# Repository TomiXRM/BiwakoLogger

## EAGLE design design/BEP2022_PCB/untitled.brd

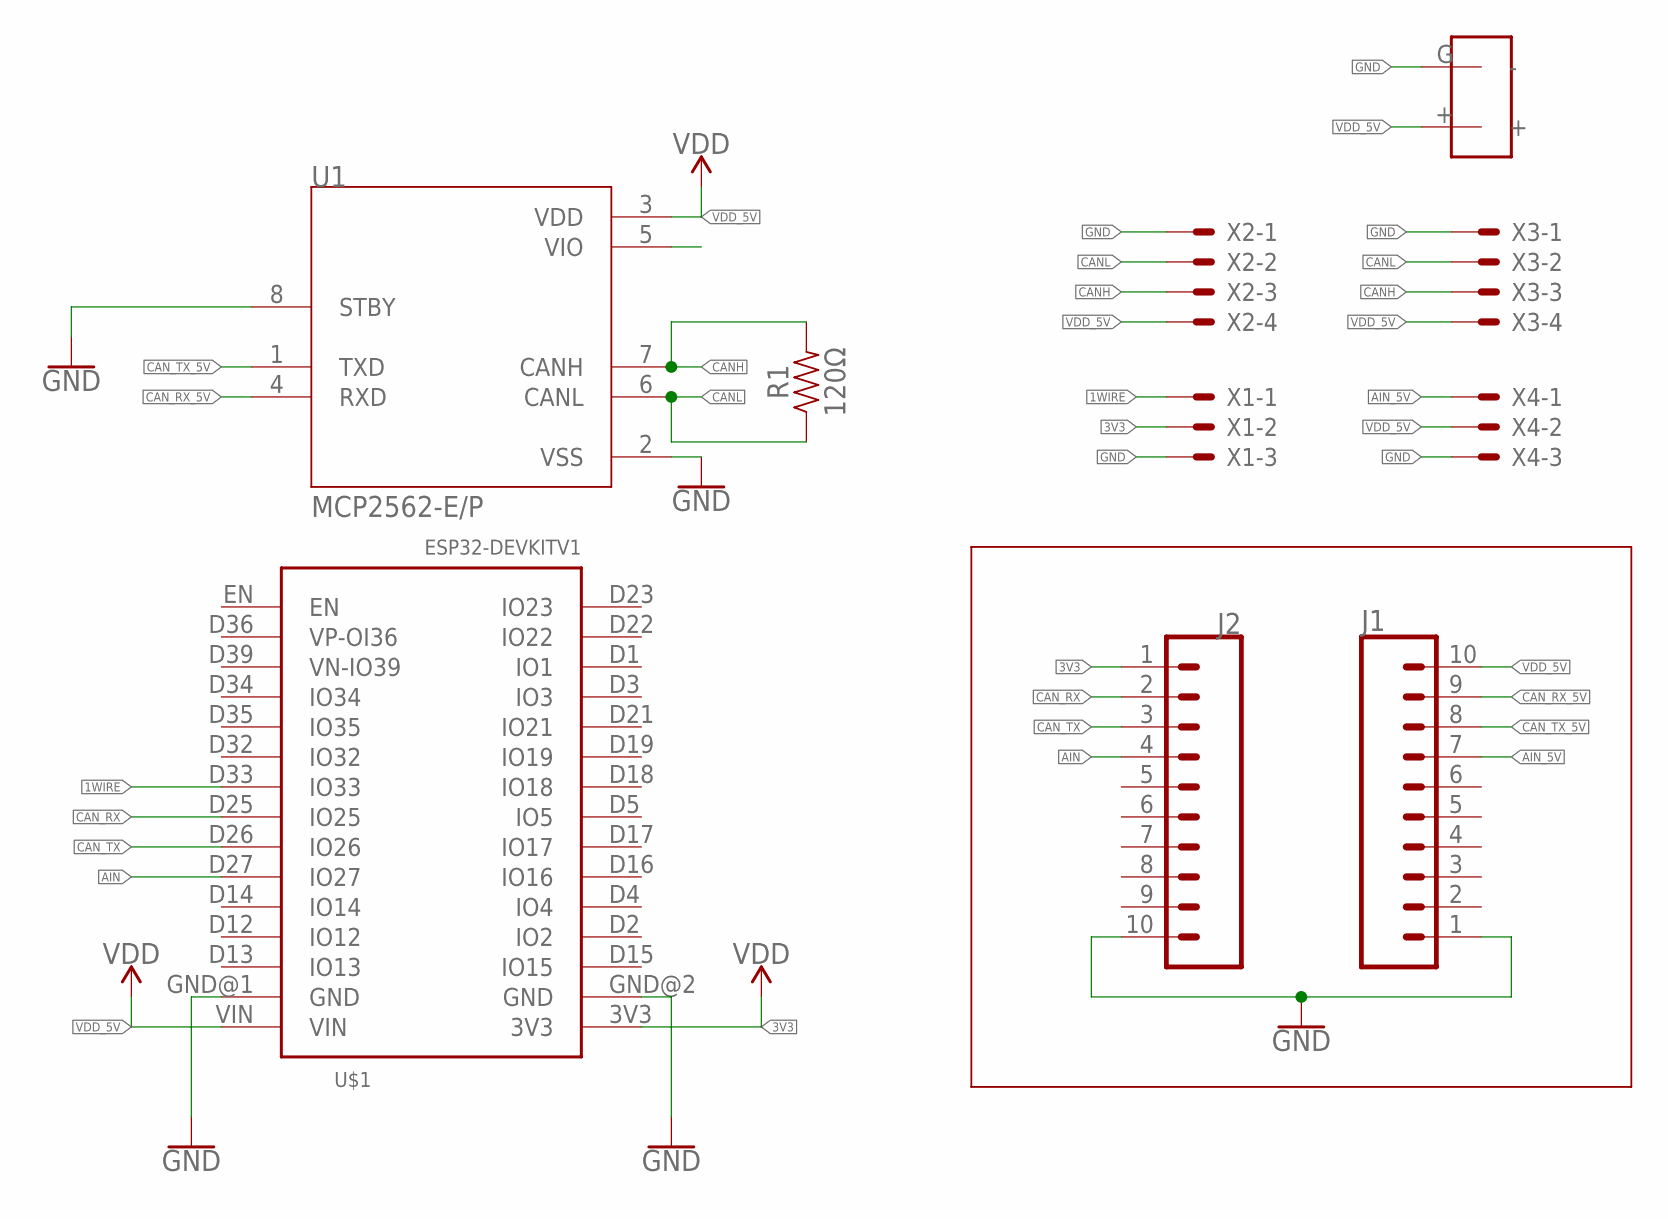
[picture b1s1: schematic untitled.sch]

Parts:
J1, J2: CONN_10"; 1X10
R1: 120Ω; AXIAL-0.3
U1: MCP2562-E/P; DIP787W45P254L1016H533Q8
U$1: ESP32DEVKITV1; ESP32-DEVKITV1
U$2: BAT
X1, X4: JST-XH-03-PIN-LONG-PAD; JST-XH-03-PACKAGE-LONG-PAD
X2, X3: JST-XH-04-PIN-LONG-PAD; JST-XH-04-PACKAGE-LONG-PAD

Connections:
1WIRE: U$1.D33 (IO33), X1.1
3V3: J2.1, U$1.3V3, X1.2
AIN: J2.4, U$1.D27 (IO27)
AIN_5V: J1.7, X4.1
CANH: R1.P$2 (2), U1.7 (CANH), X2.3, X3.3
CANL: R1.P$1 (1), U1.6 (CANL), X2.2, X3.2
CAN_RX: J2.2, U$1.D25 (IO25)
CAN_RX_5V: J1.9, U1.4 (RXD)
CAN_TX: J2.3, U$1.D26 (IO26)
CAN_TX_5V: J1.8, U1.1 (TXD)
GND: J1.1, J2.10, U1.2 (VSS), U1.8 (STBY), U$1.GND@1 (GND), U$1.GND@2 (GND), U$2.G (-), X1.3, X2.1, X3.1, X4.3
VDD_5V: J1.10, U1.3 (VDD), U$1.VIN, U$2.+, X2.4, X3.4, X4.2

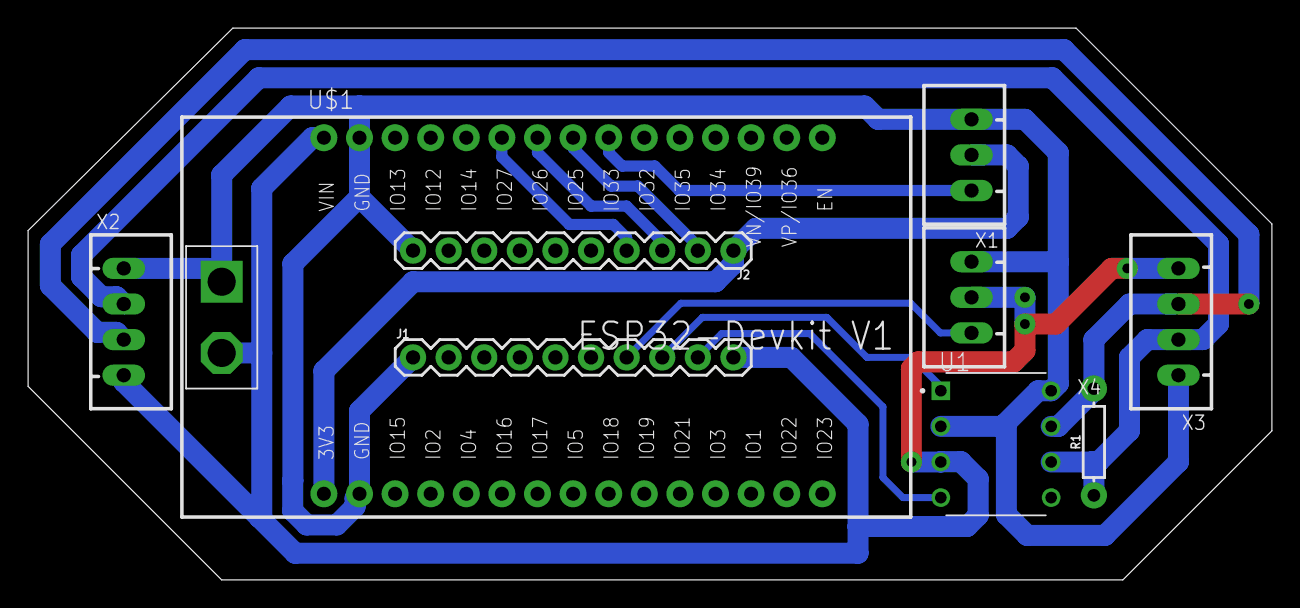
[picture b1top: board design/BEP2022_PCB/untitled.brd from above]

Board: 2 copper layers, 88.7 x 39.4 mm, 10 parts (0 on the bottom side), 12 nets.

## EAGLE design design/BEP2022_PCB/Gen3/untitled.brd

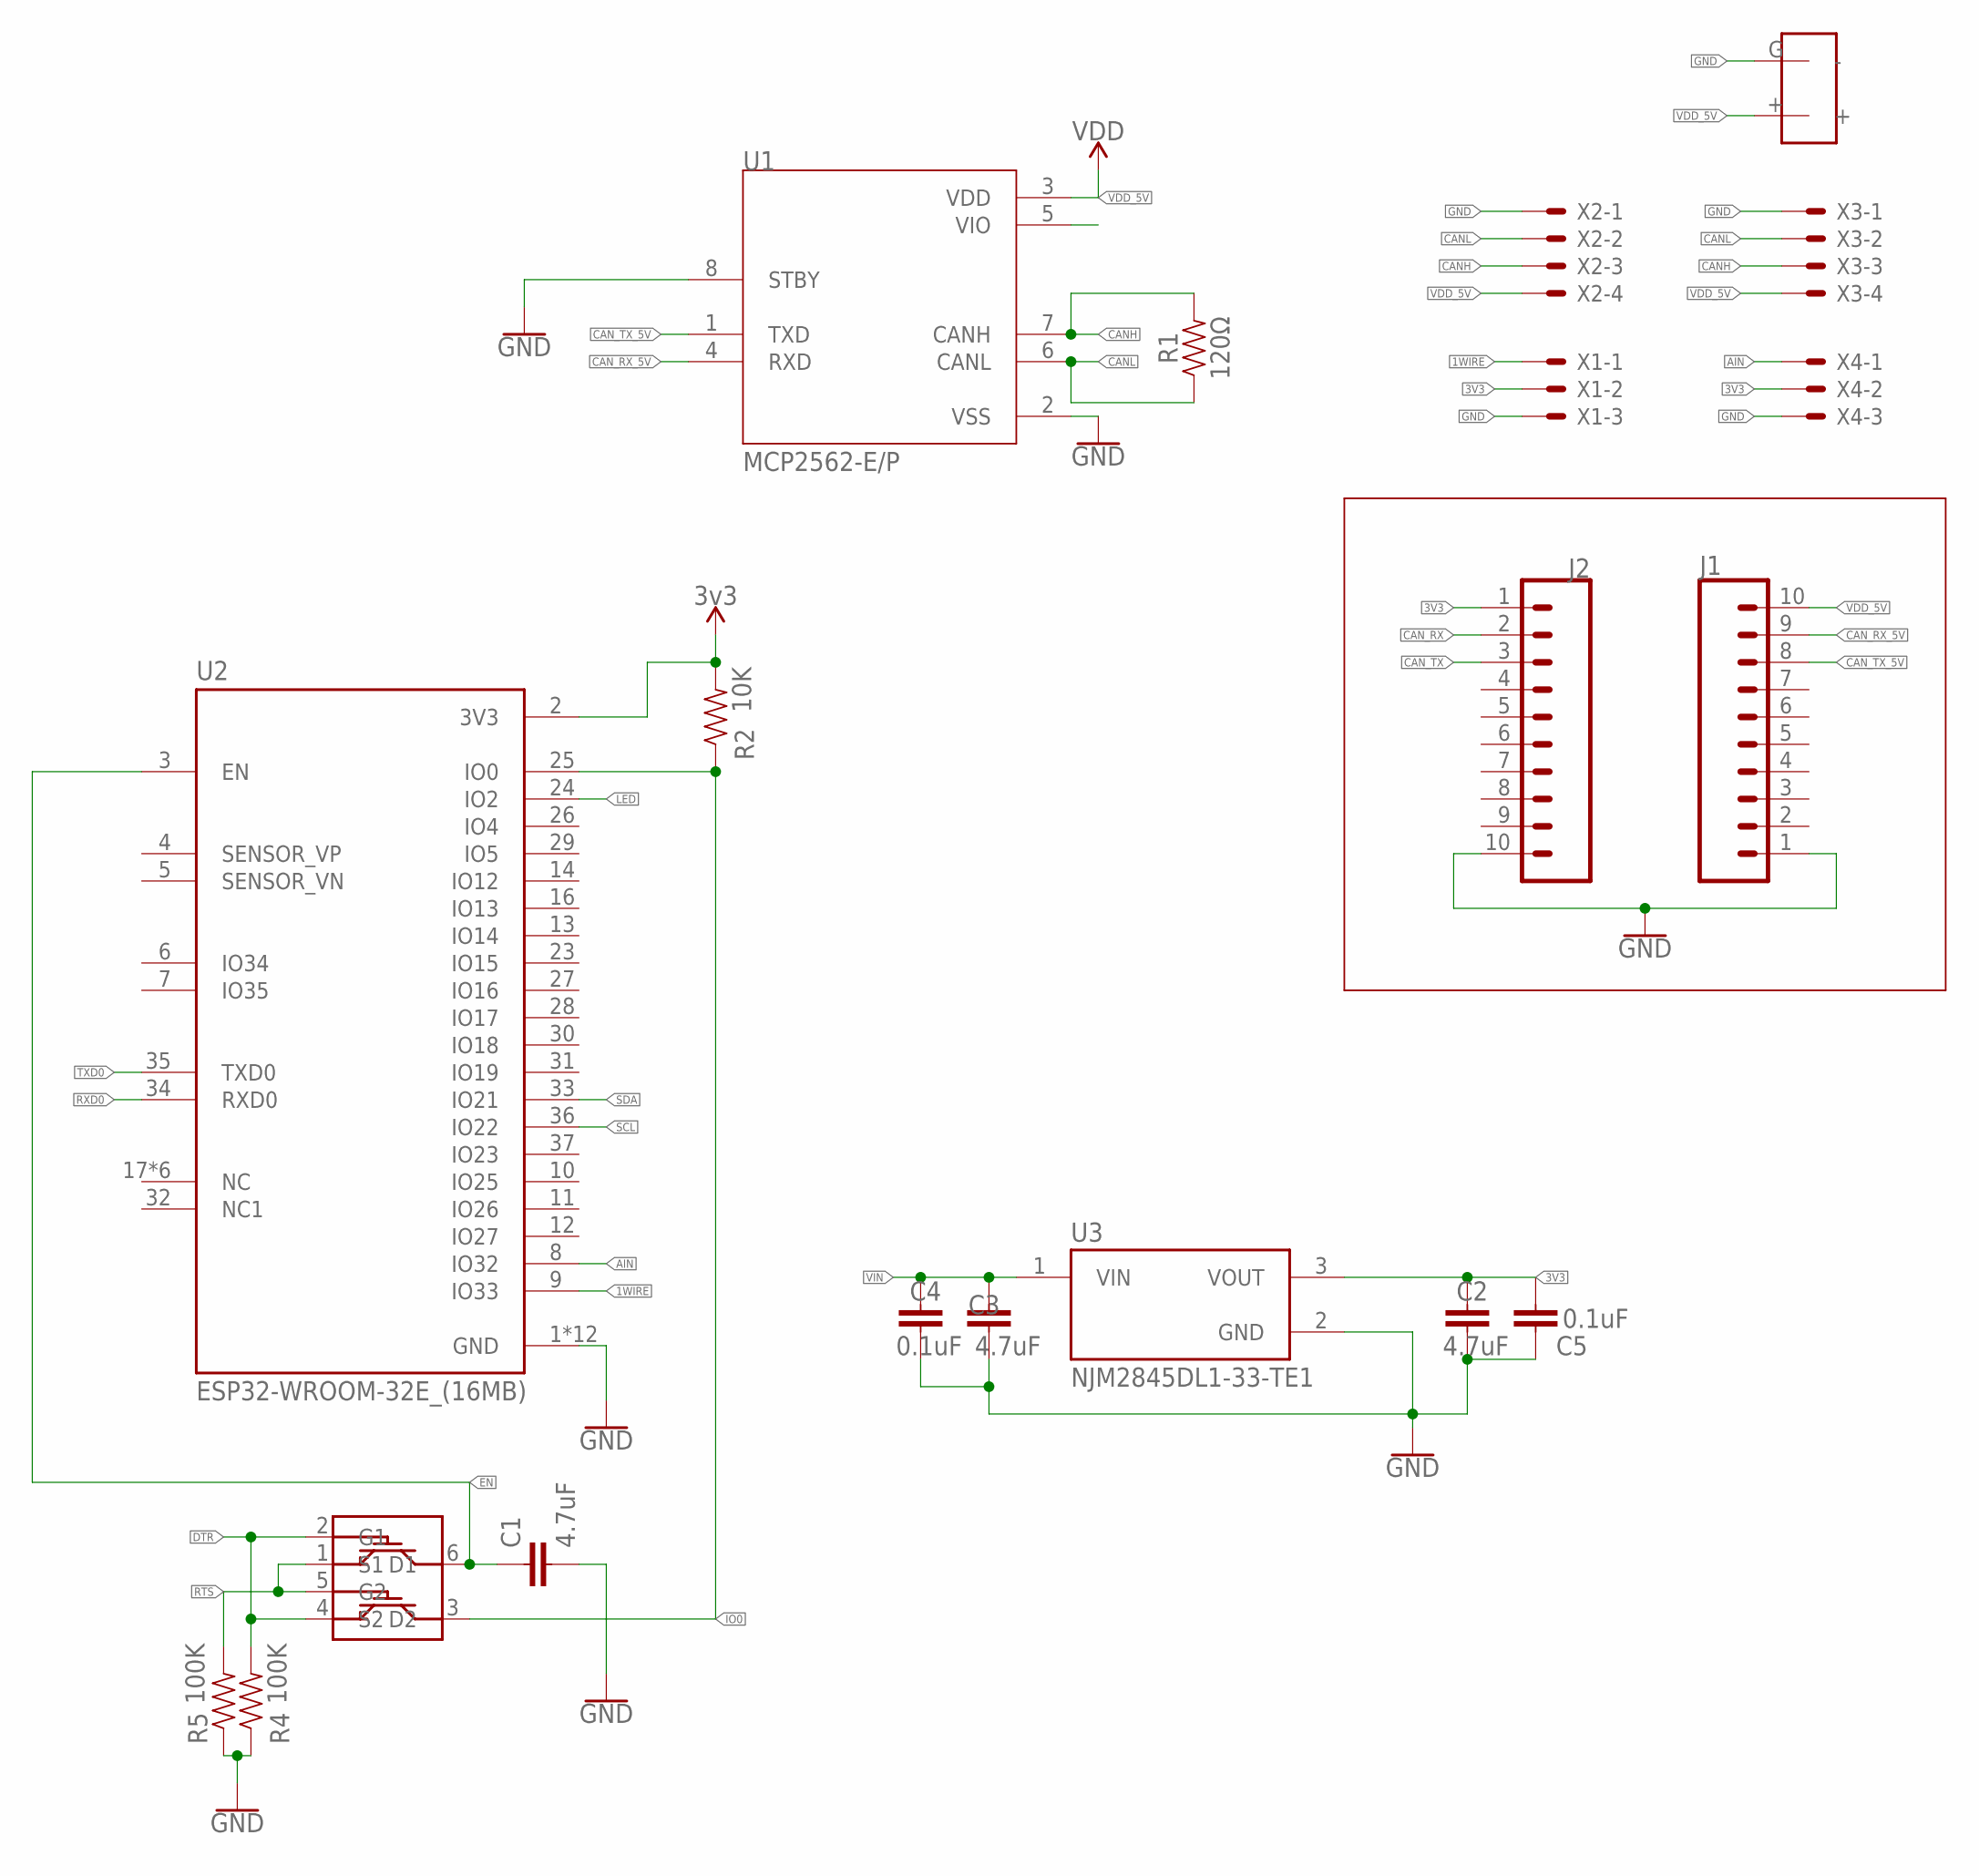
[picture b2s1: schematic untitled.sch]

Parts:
C1, C2, C3: 4.7uF; 0603
C4, C5: 0.1uF; 0603
J1, J2: CONN_10"; 1X10
R1: 120Ω; AXIAL-0.3
R2: 10K; 0603
R4, R5: 100K; 0603
U1: MCP2562-E/P; DIP787W45P254L1016H533Q8
U2: ESP32-WROOM-32E_(16MB); XCVR_ESP32-WROOM-32E_(16MB)
U3: NJM2845DL1-33-TE1; DPAK228P968X238-4N
U$1: 2N7002DW; SOT363
U$2: BAT
X1, X4: JST-XH-03-PIN-LONG-PAD; JST-XH-03-PACKAGE-LONG-PAD
X2, X3: JST-XH-04-PIN-LONG-PAD; JST-XH-04-PACKAGE-LONG-PAD

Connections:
1WIRE: U2.9 (IO33), X1.1
3V3: C2.1, C5.2, J2.1, R2.2, U2.2 (3V3), U3.3 (VOUT), X1.2, X4.2
AIN: U2.8 (IO32), X4.1
CANH: R1.P$2 (2), U1.7 (CANH), X2.3, X3.3
CANL: R1.P$1 (1), U1.6 (CANL), X2.2, X3.2
CAN_RX: J2.2
CAN_RX_5V: J1.9, U1.4 (RXD)
CAN_TX: J2.3
CAN_TX_5V: J1.8, U1.1 (TXD)
DTR: R4.2, U$1.2 (G1), U$1.4 (S2)
EN: C1.1, U2.3 (EN), U$1.6 (D1)
GND: C1.2, C2.2, C3.1, C4.2, C5.1, J1.1, J2.10, U1.2 (VSS), U1.8 (STBY), U2.1 (GND), U2.15 (GND), U2.38 (GND), U2.39_1 (GND), U2.39_2 (GND), U2.39_3 (GND), U2.39_4 (GND), U2.39_5 (GND), U2.39_6 (GND), U2.39_7 (GND), U2.39_8 (GND), U2.39_9 (GND), U3.2 (GND), U$2.G (-), X1.3, X2.1, X3.1, X4.3
IO0: R2.1, U2.25 (IO0), U$1.3 (D2)
LED: U2.24 (IO2)
unnamed: R4.1, R5.1
RTS: R5.2, U$1.1 (S1), U$1.5 (G2)
RXD0: U2.34 (RXD0)
SCL: U2.36 (IO22)
SDA: U2.33 (IO21)
TXD0: U2.35 (TXD0)
VDD_5V: J1.10, U1.3 (VDD), U$2.+, X2.4, X3.4
VIN: C3.2, C4.1, U3.1 (VIN)

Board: 2 copper layers, 20 parts (2 on the bottom side), 15 nets, no tracks yet.

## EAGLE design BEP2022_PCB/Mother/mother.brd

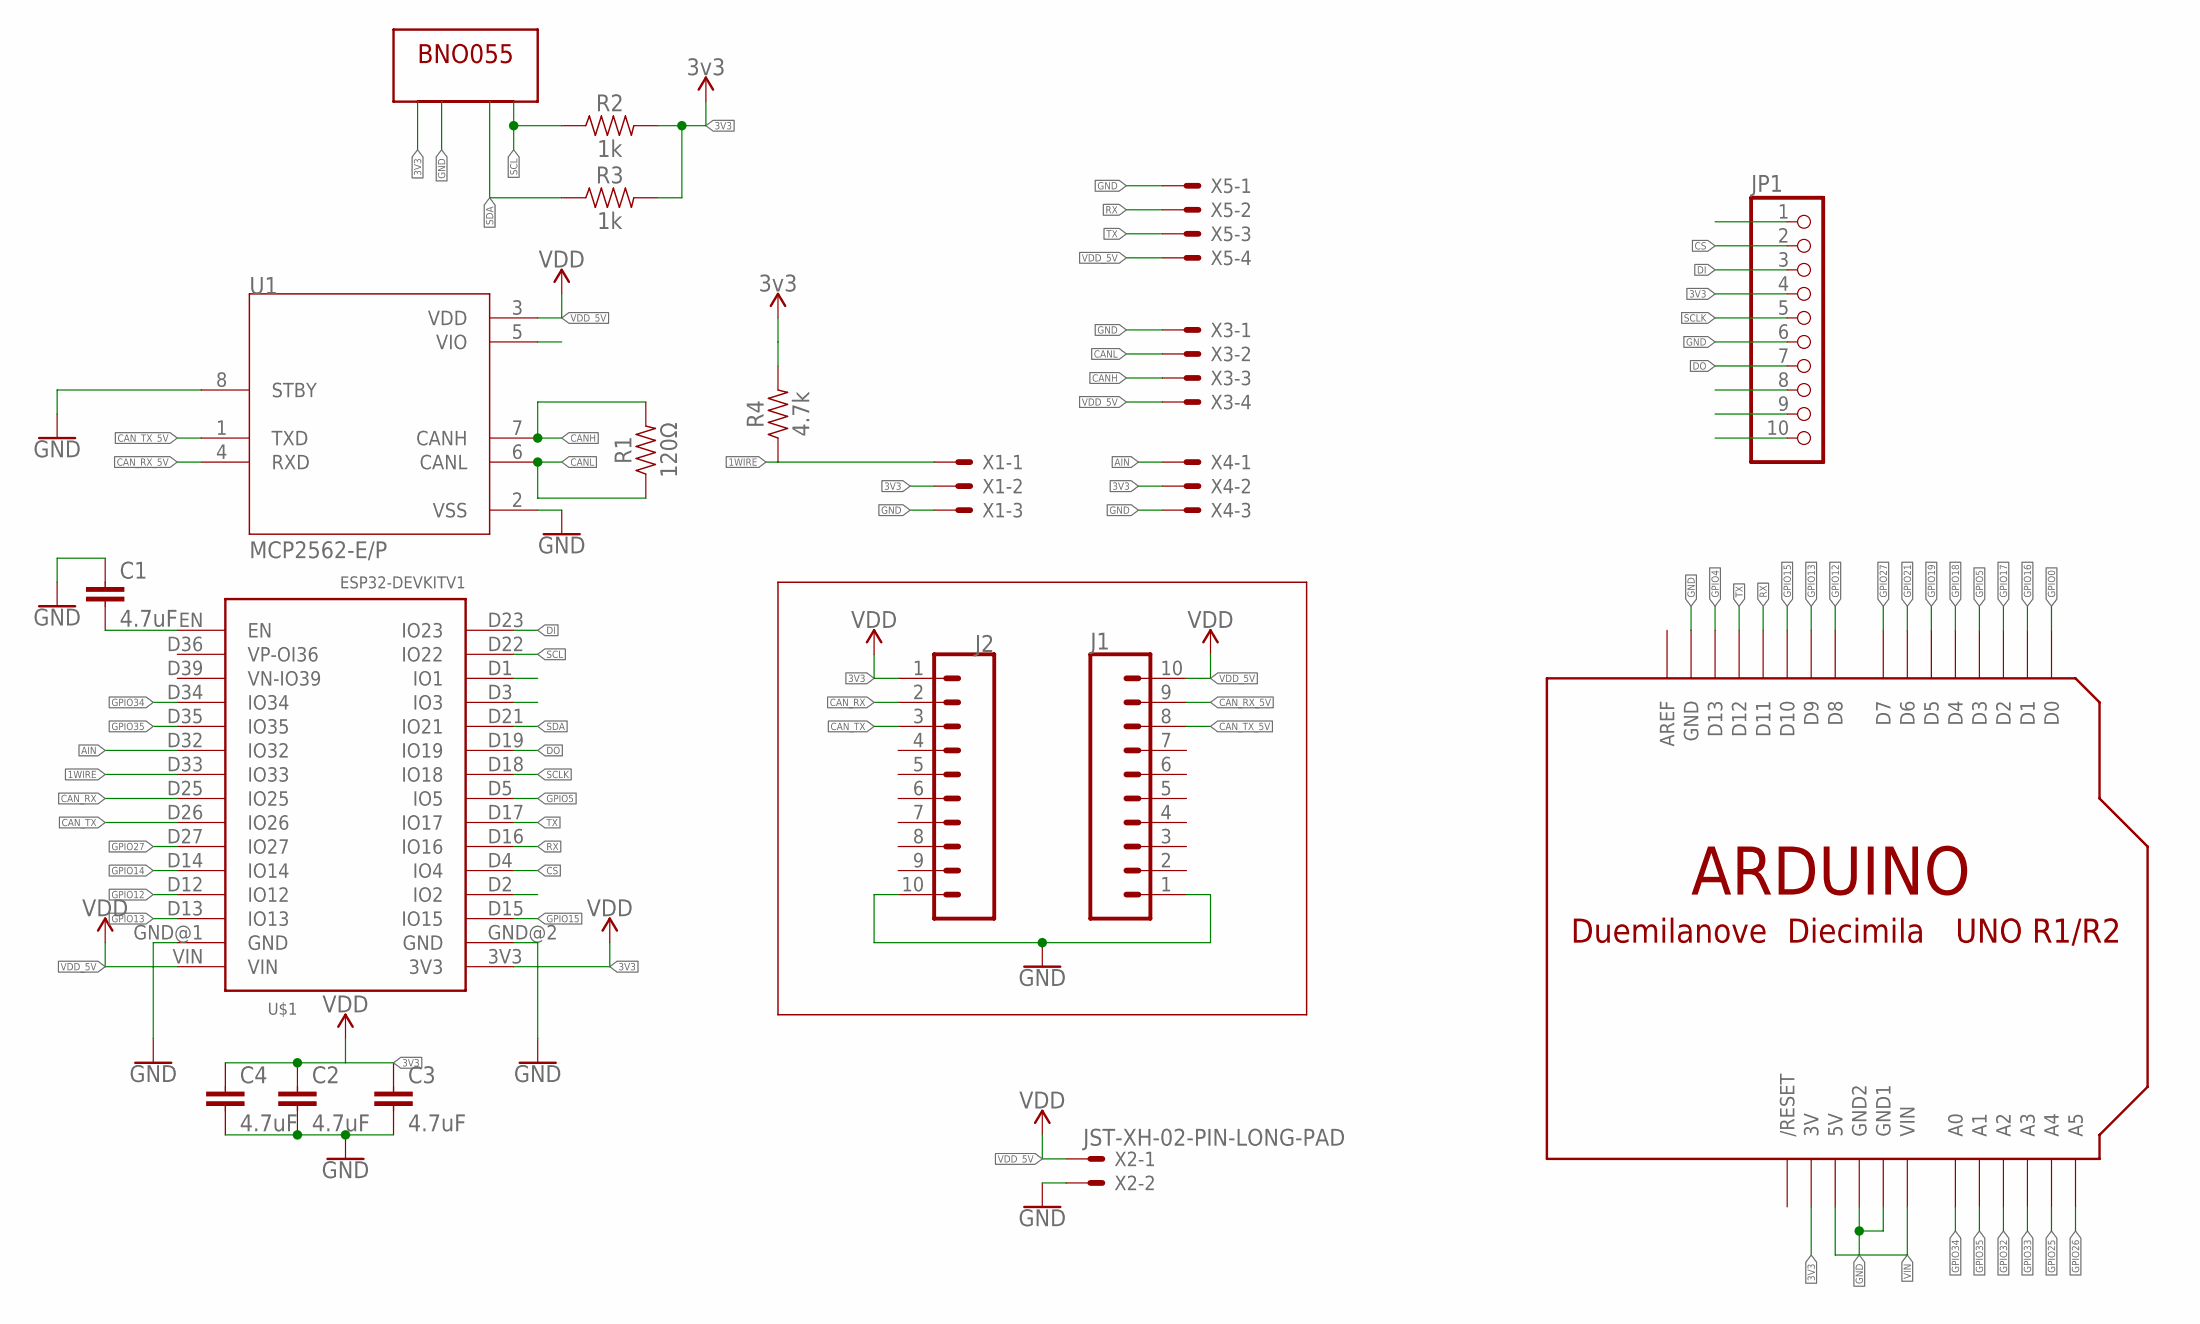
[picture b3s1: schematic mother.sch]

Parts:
C1, C2, C3, C4: 4.7uF; 0603
J1, J2: CONN_10"; 1X10
JP1: PINHD-1X10; 1X10
R1: 120Ω; AXIAL-0.3
R2, R3: 1k; 0603
R4: 4.7k; 0603
U1: MCP2562-E/P; DIP787W45P254L1016H533Q8
U$1: ESP32DEVKITV1; ESP32-DEVKITV1
U$2: ARDUINO-NOHOLE
U$3: AE-BNO055-BO
X1, X4: JST-XH-03-PIN-LONG-PAD; JST-XH-03-PACKAGE-LONG-PAD
X2: JST-XH-02-PIN-LONG-PAD; JST-XH-02-PACKAGE-LONG-PAD
X3, X5: JST-XH-04-PIN-LONG-PAD; JST-XH-04-PACKAGE-LONG-PAD

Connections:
1WIRE: R4.1, U$1.D33 (IO33), X1.1
3V3: C2.1, C3.1, C4.1, J2.1, JP1.4, R2.2, R3.2, R4.2, U$1.3V3, U$2.3V, U$3.VIN, X1.2, X4.2
AIN: U$1.D32 (IO32), X4.1
CANH: R1.P$2 (2), U1.7 (CANH), X3.3
CANL: R1.P$1 (1), U1.6 (CANL), X3.2
CAN_RX: J2.2, U$1.D25 (IO25)
CAN_RX_5V: J1.9, U1.4 (RXD)
CAN_TX: J2.3, U$1.D26 (IO26)
CAN_TX_5V: J1.8, U1.1 (TXD)
CS: JP1.2, U$1.D4 (IO4)
DI: JP1.3, U$1.D23 (IO23)
DO: JP1.7, U$1.D19 (IO19)
EN: C1.2, U$1.EN
GND: C1.1, C2.2, C3.2, C4.2, J1.1, J2.10, JP1.6, U1.2 (VSS), U1.8 (STBY), U$1.GND@1 (GND), U$1.GND@2 (GND), U$2.GND, U$2.GND1, U$2.GND2, U$3.GND, X1.3, X2.2, X3.1, X4.3, X5.1
GPIO0: U$2.D0
GPIO1: U$1.D1 (IO1)
GPIO4: U$2.D13
GPIO5: U$1.D5 (IO5), U$2.D3
GPIO12: U$1.D12 (IO12), U$2.D8
GPIO13: U$1.D13 (IO13), U$2.D9
GPIO14: U$1.D14 (IO14)
GPIO15: U$1.D15 (IO15), U$2.D10
GPIO16: U$2.D1
GPIO17: U$2.D2
GPIO18: U$2.D4
GPIO19: U$2.D5
GPIO21: U$2.D6
GPIO25: U$2.A4
GPIO26: U$2.A5
GPIO27: U$1.D27 (IO27), U$2.D7
GPIO32: U$2.A2
GPIO33: U$2.A3
GPIO34: U$1.D34 (IO34), U$2.A0
GPIO35: U$1.D35 (IO35), U$2.A1
RX: U$1.D16 (IO16), U$2.D11, X5.2
SCL: R2.1, U$1.D22 (IO22), U$3.SCL
SCLK: JP1.5, U$1.D18 (IO18)
SDA: R3.1, U$1.D21 (IO21), U$3.SDA
TX: U$1.D17 (IO17), U$2.D12, X5.3
VDD_5V: J1.10, U1.3 (VDD), U$1.VIN, X2.1, X3.4, X5.4
VIN: U$2.5V, U$2.VIN

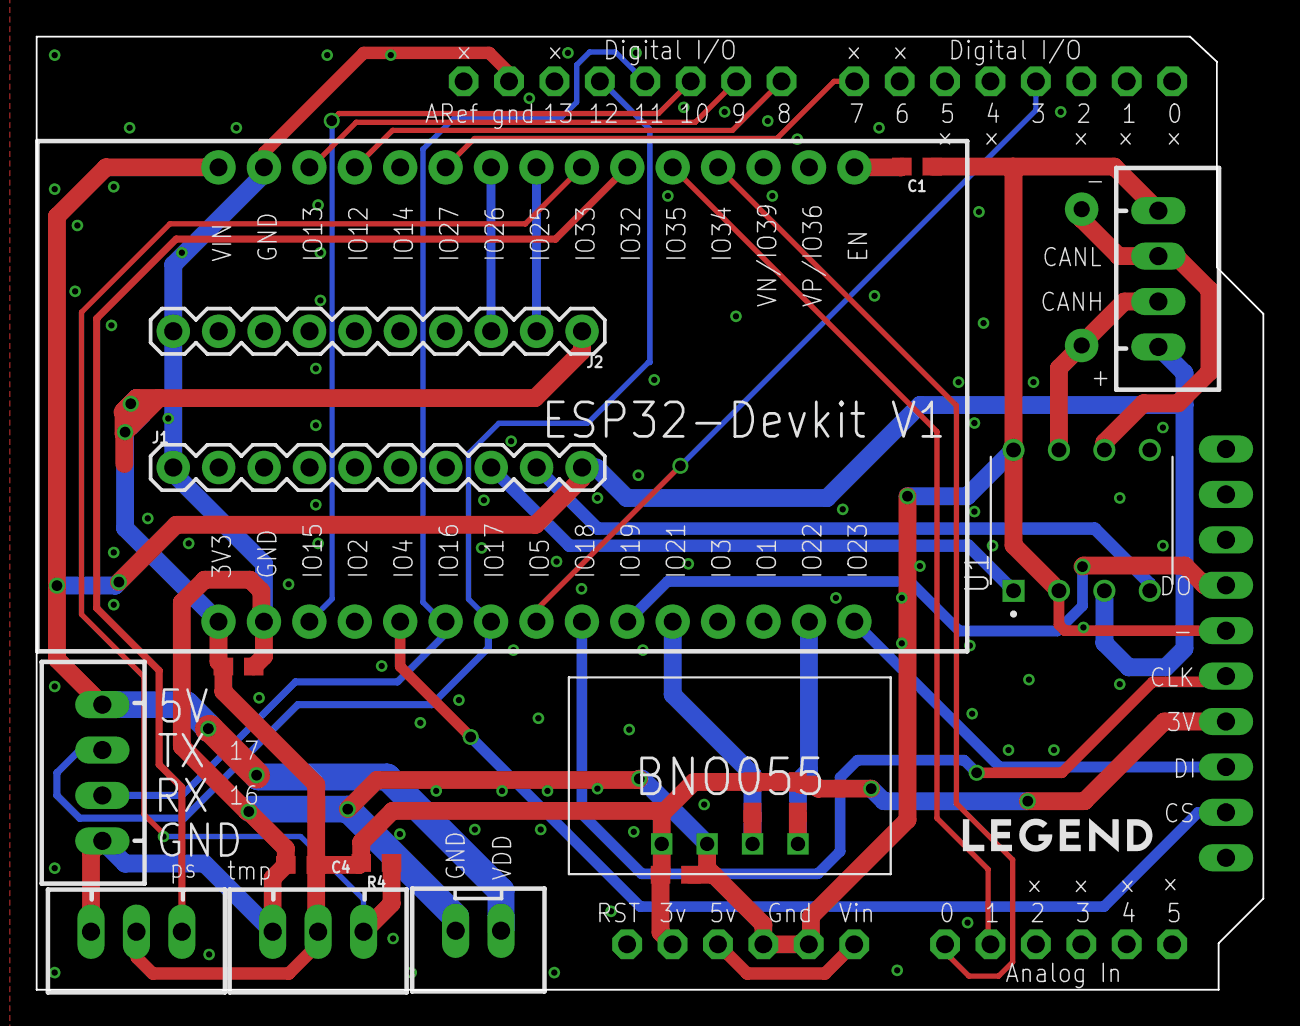
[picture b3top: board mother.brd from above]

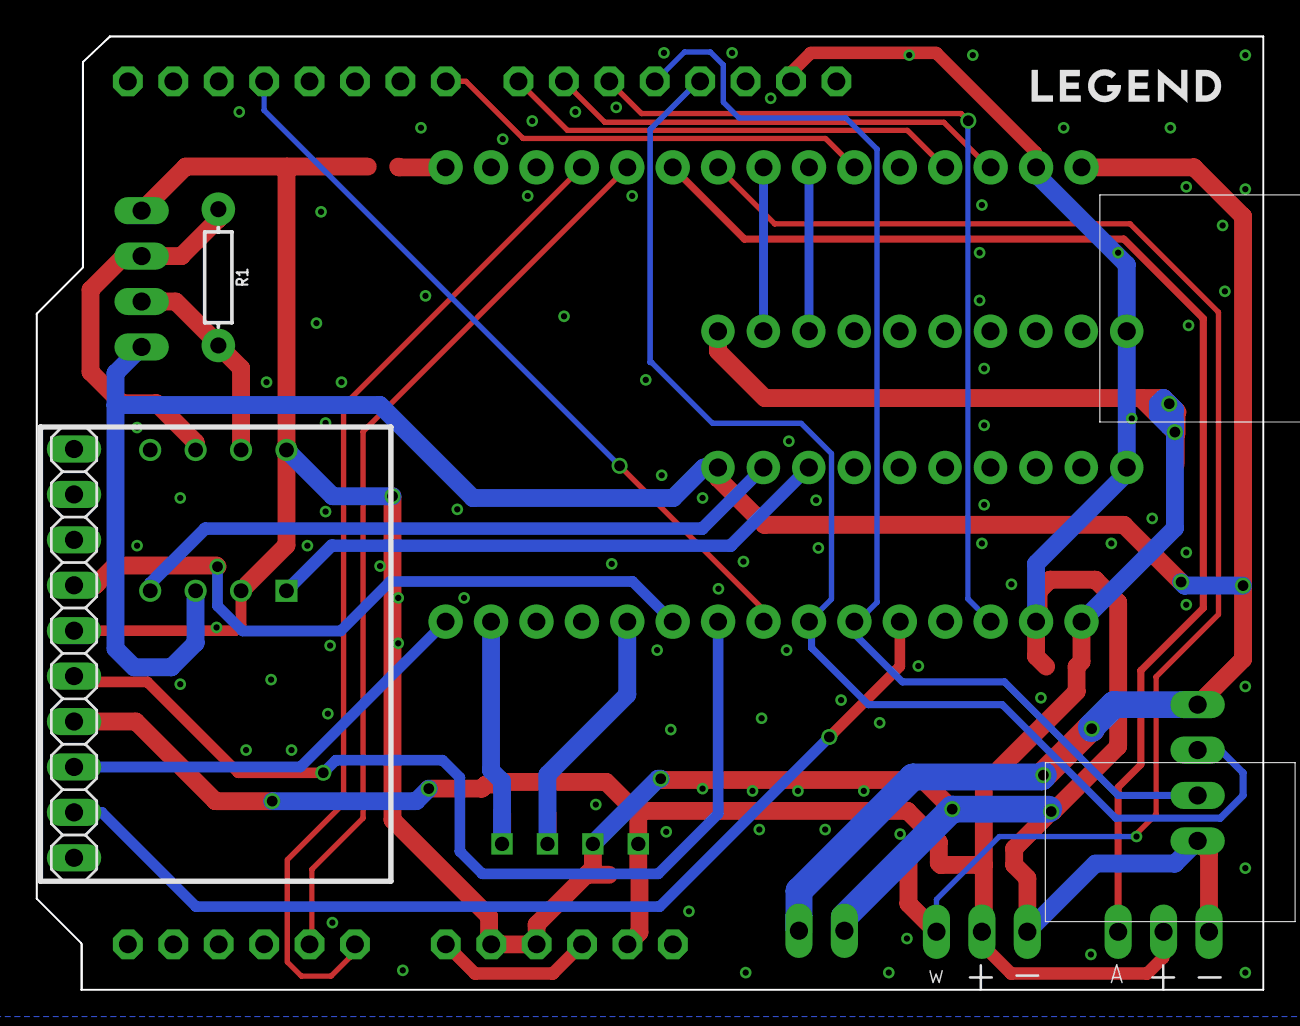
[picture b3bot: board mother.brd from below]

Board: 2 copper layers, 68.6 x 53.3 mm, 20 parts (2 on the bottom side), 28 nets.

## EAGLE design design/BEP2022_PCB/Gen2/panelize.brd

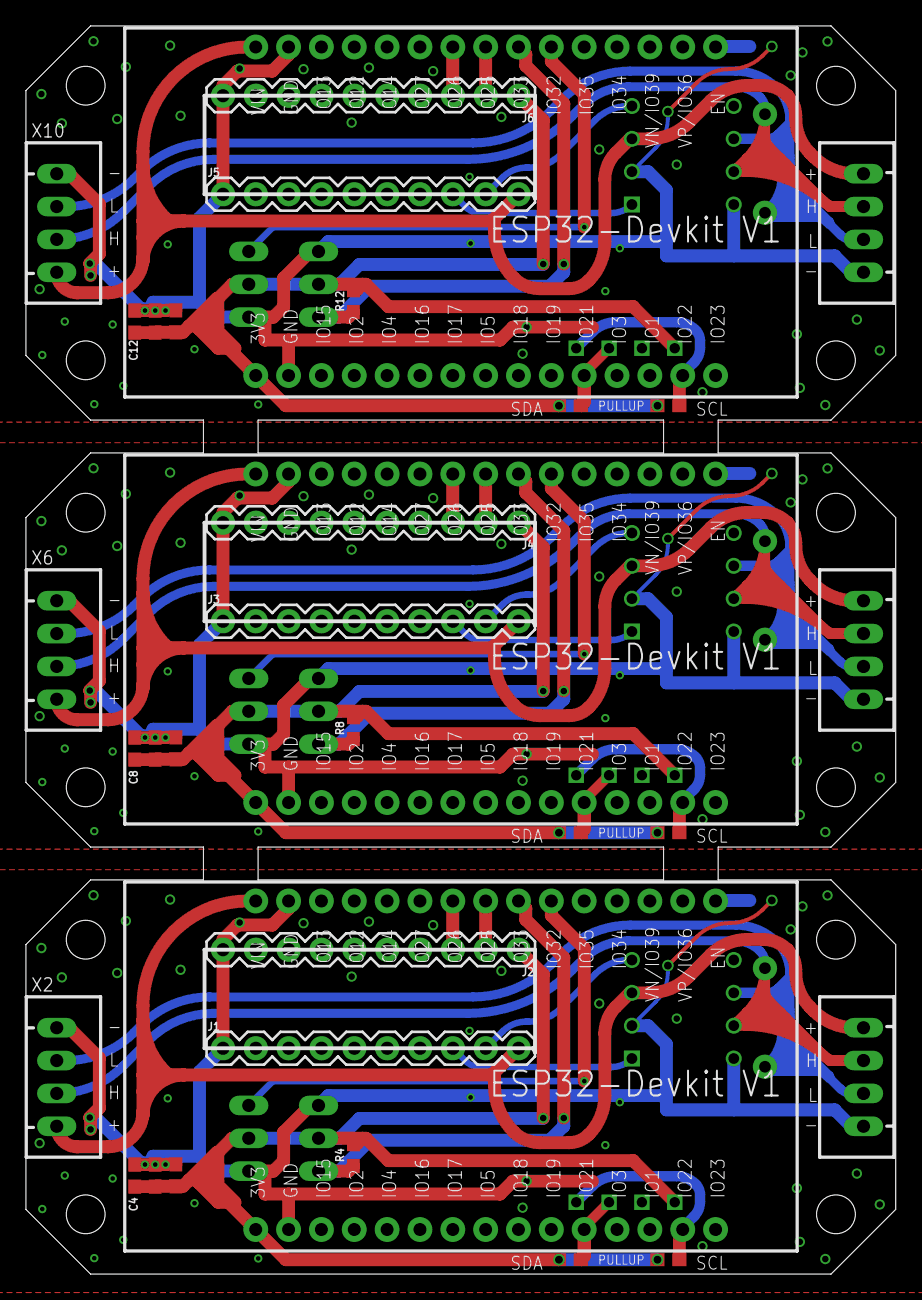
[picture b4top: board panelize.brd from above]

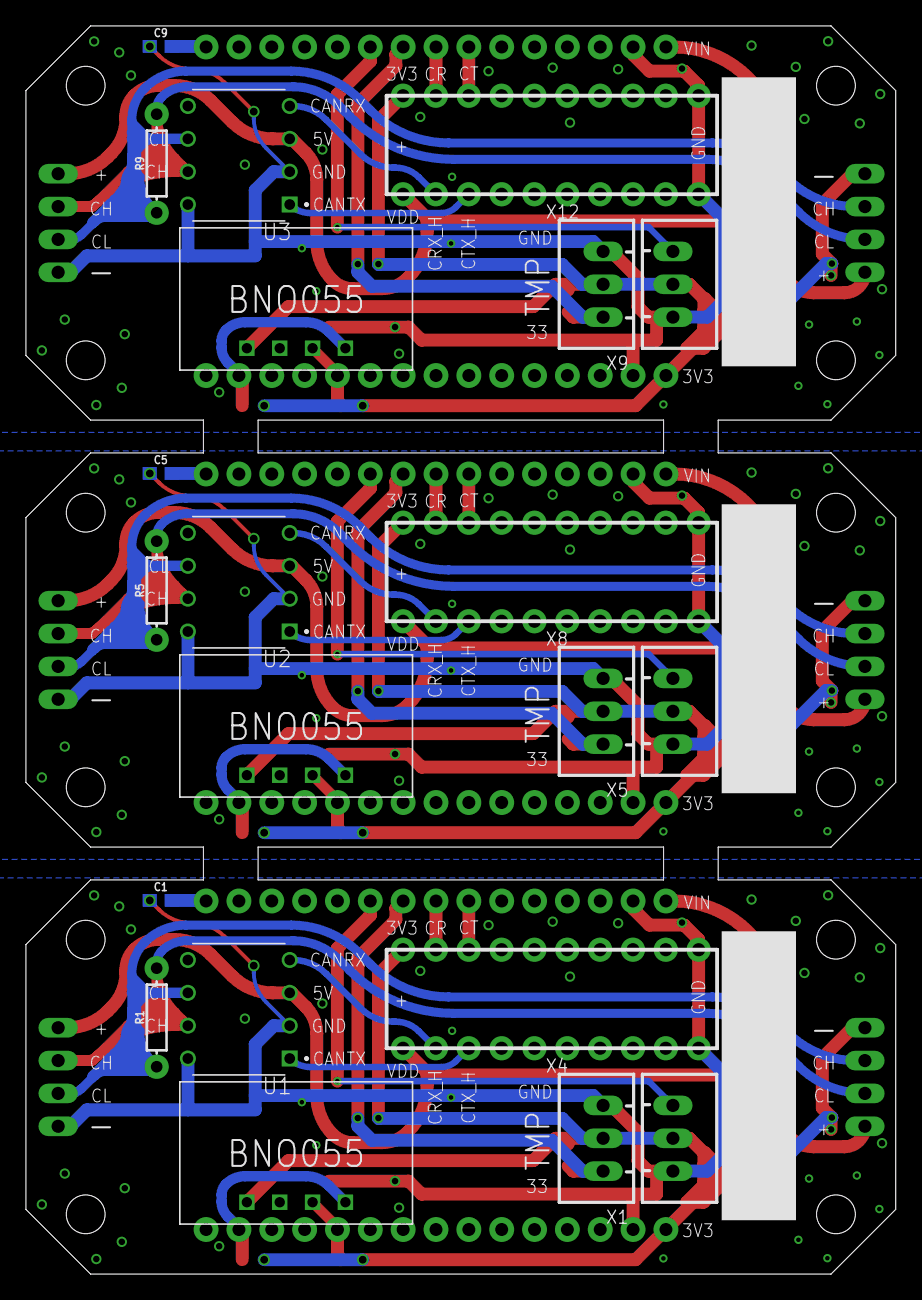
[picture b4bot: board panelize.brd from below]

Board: 2 copper layers, 67.3 x 96.5 mm, 51 parts (18 on the bottom side), 42 nets.

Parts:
C1, C2, C3, C4, C5, C6, C7, C8, C9, C10, C11, C12: 4.7uF; 0603
J1, J2, J3, J4, J5, J6: 1X10
R1, R5, R9: 120Ω; AXIAL-0.3
R2, R3, R6, R7, R10, R11: 1k; 0603
R4, R8, R12: 4.7k; 0603
U1, U2, U3: MCP2562-E/P; DIP787W45P254L1016H533Q8
U$1, U$2, U$5: ESP32DEVKITV1; ESP32-DEVKITV1
U$3, U$4, U$6: AE-BNO055-BO
X1, X4, X5, X8, X9, X12: JST-XH-03-PIN-LONG-PAD; JST-XH-03-PACKAGE-LONG-PAD
X2, X3, X6, X7, X10, X11: JST-XH-04-PIN-LONG-PAD; JST-XH-04-PACKAGE-LONG-PAD

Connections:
1WIRE: R4.1, U$1.D33, X1.1
1WIRE1: R8.1, U$2.D33, X5.1
1WIRE2: R12.1, U$5.D33, X9.1
3V1: C6.1, C7.1, C8.1, J4.1, R6.2, R7.2, R8.2, U$2.3V3, U$4.VIN, X5.2, X8.2
3V2: C10.1, C11.1, C12.1, J6.1, R10.2, R11.2, R12.2, U$5.3V3, U$6.VIN, X9.2, X12.2
3V3: C2.1, C3.1, C4.1, J2.1, R2.2, R3.2, R4.2, U$1.3V3, U$3.VIN, X1.2, X4.2
AIN: U$1.D32, X4.1
AIN1: U$2.D32, X8.1
AIN2: U$5.D32, X12.1
CANH: R1.P$2, U1.7, X2.3, X3.3
CANH1: R5.P$2, U2.7, X6.3, X7.3
CANH2: R9.P$2, U3.7, X10.3, X11.3
CANL: R1.P$1, U1.6, X2.2, X3.2
CANL1: R5.P$1, U2.6, X6.2, X7.2
CANL2: R9.P$1, U3.6, X10.2, X11.2
CAN_RX: J2.2, U$1.D25
CAN_RX1: J4.2, U$2.D25
CAN_RX2: J6.2, U$5.D25
CAN_RX_5V: J1.9, U1.4
CAN_RX_5V1: J3.9, U2.4
CAN_RX_5V2: J5.9, U3.4
CAN_TX: J2.3, U$1.D26
CAN_TX1: J4.3, U$2.D26
CAN_TX2: J6.3, U$5.D26
CAN_TX_5V: J1.8, U1.1
CAN_TX_5V1: J3.8, U2.1
CAN_TX_5V2: J5.8, U3.1
EN: C1.2, U$1.EN
EN1: C5.2, U$2.EN
EN2: C9.2, U$5.EN
GND: C1.1, C2.2, C3.2, C4.2, J1.1, J2.10, U1.2, U1.8, U$1.GND@1, U$1.GND@2, U$3.GND, X1.3, X2.1, X3.1, X4.3
GND1: C5.1, C6.2, C7.2, C8.2, J3.1, J4.10, U2.2, U2.8, U$2.GND@1, U$2.GND@2, U$4.GND, X5.3, X6.1, X7.1, X8.3
GND2: C9.1, C10.2, C11.2, C12.2, J5.1, J6.10, U3.2, U3.8, U$5.GND@1, U$5.GND@2, U$6.GND, X9.3, X10.1, X11.1, X12.3
SCL: R2.1, U$1.D22, U$3.SCL
SCL1: R6.1, U$2.D22, U$4.SCL
SCL2: R10.1, U$5.D22, U$6.SCL
SDA: R3.1, U$1.D21, U$3.SDA
SDA1: R7.1, U$2.D21, U$4.SDA
SDA2: R11.1, U$5.D21, U$6.SDA
VDD_5V: J1.10, U1.3, U$1.VIN, X2.4, X3.4
VDD_5V1: J3.10, U2.3, U$2.VIN, X6.4, X7.4
VDD_5V2: J5.10, U3.3, U$5.VIN, X10.4, X11.4

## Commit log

2022-06-05 add program files
2022-06-05 hello world
2022-06-05 add TinyGPS++
2022-06-05 GPSで緯度経度が読めた
2022-06-05 add SD library
2022-06-05 GPSの受信に成功した
2022-06-05 interrupts()を使うと割り込み関数内でSerialクラスとかも使えるようになるらしいので追加した
    https://www.renesas.com/jp/ja/products/gadget-renesas/reference/gr-adzuki/library-interrupt
2022-07-13 add ESP32 CAN Test
2022-07-29 reciver通信成功
2022-08-01 add n new file
2022-08-01 master slave
2022-08-12 速度計を作ってみた
2022-08-12 コメントを追加
2022-08-13 基板を追加
2022-08-14 マルチタスクで温度センサを取得するプログラムの動作成功
2022-08-16 update PCB
2022-08-19 母機の基板設計をした
2022-08-19 3Dデータを追加した
2022-08-22 基板のアップデート
2022-08-23 Serial1を使うことに成功
2022-08-28 Gerber update
2022-09-06 program updates
2022-09-06 panelized update
    細すぎた
2022-09-09 CAN通信成功
2022-09-13 GPSをESP32で読んだ
2022-09-13 非同期でもGPSを受信できることがわかった
2022-09-14 WIP:IMUキャリブレーションとモード切り替えの実装
2022-09-27 CANで8byte送るやつやった。double
2022-09-27 Bluetoothに対応したのと重力加速度のフィルタリングバージョンと重力加速度モードを追加
2022-09-27 WIP.CANで送信するクソデカバイト列でお悩み中
2022-10-02 ファイルの移動と整理をした。
2022-10-02 Create files
2022-10-02 dataDefs内でデータ管理クラスを作成した。
    https://rionessl.notion.site/02a1473910c543d1b09990573454908a
2022-10-02 main.cppでデータ管理クラスを宣言させた
2022-10-02 systemManageの更新
2022-10-04 WIP sensors.hpp
2022-10-05 systemManagerのリファクタリング完了
2022-10-06 WIP ビルド通った
2022-10-06 文字の修正をした
2022-10-09 センサ読み取りの抽象化をした
2022-10-10 WIP:自作ライブラリ突っ込まなかったら動いた
2022-10-10 コンストラクタデカすぎたら動かなかった
2022-10-10 クソデカコンストラクタをやめたらsysManも動いた
2022-10-10 canSenderもbeginを追加して対処した
2022-10-10 Lチカ成功！！！！！！
2022-10-22 add print()
2022-10-22 change namings of Class into PascalCase
2022-10-22 change name "Loger" into "Logger" and add Mother
2022-10-23 Success query & send-receive with ID from mother
2022-10-23 Fix: problem with temperature sensor reading
2022-10-23 add dataDefs
2022-10-24 Success:recieving CAN on Mother with each data
2022-10-24 :pencil2: set interval
2022-10-25 :sparkles: Add ArduinoLog
2022-10-25 some fix
    # ==== Emojis ====
    # ✨ :sparkles: Add new feature
    # ✅ :white_check_mark: Update existing feature (not bug)
    # ⚠️ :warning: Fix bug/error
    # 🔥 :fire: Remove files or features
    # ✏️ :pencil2: Fix typos
2022-10-26 ビルド通ったけどメモリエラー発生
2022-10-27 WIPちょとプリントデバッグ追加した
2022-10-27 WIPビルド通ったけどfloatがちゃんと代入されない。
2022-10-28 :warning: Fix bug ArduinoLogでのFloatデバッグ廃止
2022-10-28 :warning: solve Debug problem
2022-10-28 :white_check_mark: support multiple Loggers
2022-10-28 ✨ :sparkles: Add error handling at receive event
    # ==== Emojis ====
    # ✨ :sparkles: Add new feature
    # ✅ :white_check_mark: Update existing feature (not bug)
    # ⚠️ :warning: Fix bug/error
    # 🔥 :fire: Remove files or features
    # ✏️ :pencil2: Fix typos
2022-10-28 :sparkles: recieving data with CAN IRQ
    # ==== Emojis ====
    # ✨ :sparkles: Add new feature
    # ✅ :white_check_mark: Update existing feature (not bug)
    # ⚠️ :warning: Fix bug/error
    # 🔥 :fire: Remove files or features
    # ✏️ :pencil2: Fix typos
2022-10-28 :white_check_mark: Support print values
    # ==== Emojis ====
    # ✨ :sparkles: Add new feature
    # ✅ :white_check_mark: Update existing feature (not bug)
    # ⚠️ :warning: Fix bug/error
    # 🔥 :fire: Remove files or features
    # ✏️ :pencil2: Fix typos
2022-10-31 コメントアウト外した

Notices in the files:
parts and their libraries:
SparkFun-PowerSymbols: Licensing: Creative Commons ShareAlike 4.0 International - https://creativecommons.org/licenses/by-sa/4.0
